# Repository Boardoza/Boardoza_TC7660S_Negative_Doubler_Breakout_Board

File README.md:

# Boardoza TC7660S Negative Doubler Breakout Board

The **Boardoza TC7660S Negative Doubler Breakout Board** is a compact voltage conversion solution based on the **TC7660S** charge pump IC. It is designed to generate a **stable negative voltage (-VOUT)** and a  **doubled negative voltage (-2VOUT)** from a positive input supply without requiring inductors.

Using a switched-capacitor voltage converter architecture, this board efficiently inverts and doubles the input voltage, making it ideal for low-current precision analog applications. It is especially well-suited for powering operational amplifiers, sensor signal conditioning circuits, and instrumentation systems where a clean and stable negative supply is required. With a typical output capability of up to **10 mA**, it is optimized for reference and low-power analog designs rather than high-current loads.

## [Click here to purchase!](https://www.ozdisan.com/ureticiler/boardoza)
| Front Side | Back Side |
| :---: | :---: |
|  |  |

---

## Key Features

- **Negative Voltage Generation:** Converts a single positive supply into stable negative voltage outputs.
- **Dual Output Capability:** Provides both -VOUT and -2VOUT options for flexible circuit design.
- **High Efficiency Charge Pump:** Achieves very high efficiency under light load conditions.
- **Low Power Consumption:** Optimized for precision, low-current applications.
- **Precision Focused Design:** Ideal for clean and stable reference voltage generation.

---

## Technical Specifications

**Model:** TC7660S-NegativeDoubler  
**Manufacturer:** Boardoza   
**Manufacturer IC:** Microchip Technology Inc.  
**Functions:** Negative voltage regulator  
**Input Voltage:** 1.5 V – 12 V  
**Voltage Input Type:** 2.50 mm pin header  
**Output Current:** 10 mA  
**Conversion Type:** Switched-capacitor charge pump  
**Oscillator Frequency:** Between 10 kHz to 45 kHz    
**Efficiency:** Up to 98–99% (typical, light load)  
**Operating Temperature:** -40 °C to +80 °C  
**Board Dimensions:** 40 mm × 20 mm

---

## Board Pinout

### ( J1 ) Power Input Connector

| Pin Number | Pin Name | Description |
| --- | --- | --- |
| 1 | VIN | Positive input voltage (1.5V – 12V) |
| 2 | GND | Ground |

### ( J2 ) Output Connector

| Pin Number | Pin Name | Description |
| --- | --- | --- |
| 1 | -2VOUT | Negative output, twice the input voltage |
| 2 | GND | Ground |
| 3 | -VOUT | Negative output, equal to input voltage |

---

## Board Dimensions

---

## Step Files

[Boardoza TC7660S-NegativeDoubler.step](./assets/TC7660S-NegativeDoubler%20Step.step)

---

## Datasheet

[TC7660S Datasheet.pdf](./assets/TC7660S-NegativeDoubler%20Datasheet.pdf)

---

## Version History

- V1.0.0 – Initial Release

---

## Support

- If you have any questions or need support, please contact **support@boardoza.com**

---

## **License**
### **Hardware Design**

[![CC BY-SA 4.0][cc-by-sa-shield]][cc-by-sa]

All hardware design files are licensed under [Creative Commons Attribution-ShareAlike 4.0 International License][cc-by-sa].

[cc-by-sa]: http://creativecommons.org/licenses/by-sa/4.0/
[cc-by-sa-shield]: https://img.shields.io/badge/License-CC%20BY--SA%204.0-lightgrey.svg

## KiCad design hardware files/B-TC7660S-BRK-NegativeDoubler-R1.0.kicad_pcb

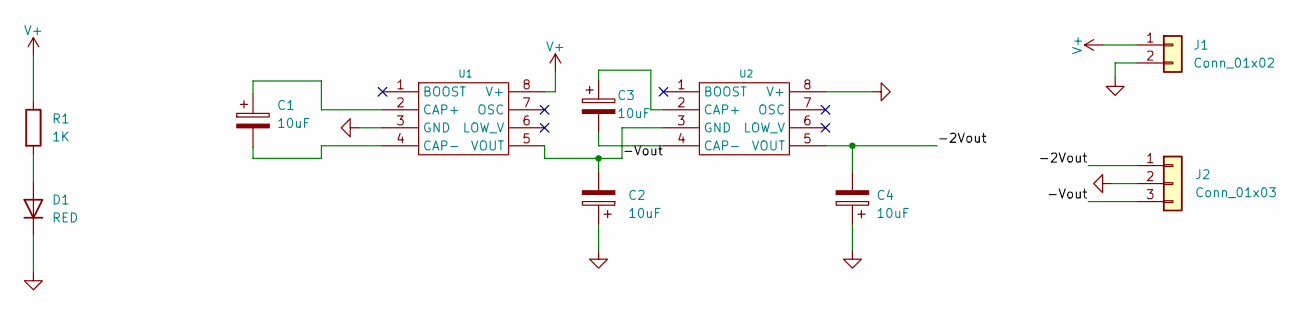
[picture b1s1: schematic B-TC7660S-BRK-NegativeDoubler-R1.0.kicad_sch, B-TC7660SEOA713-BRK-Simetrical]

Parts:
C1, C2, C3, C4: 10uF; CP_Elec_6.3x5.4; MPN JCS1H100M063054
D1: RED; D_0603_1608Metric; MPN LTST-C190KRKT
J1: Conn_01x02; 2317-02S_1x02_P2.50mm_Vertical; MPN 2317-02S
J2: Conn_01x03; 2317-03S_1x03_P2.50mm_Vertical; MPN 2317-03S
R1: 1K; R_0603_1608Metric; MPN PS03W4F1001T5E
U1, U2: SOIC127P599X175-8N; MPN TC7660SEOA713

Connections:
/-2Vout: C4.2, J2.1, U2.5 (VOUT)
/-Vout: C2.2, J2.3, U1.5 (VOUT), U2.3 (GND)
GND: C2.1, C4.1, D1.1 (K), J1.2, J2.2, U1.3 (GND), U2.8 (V+)
unnamed: D1.2 (A), R1.2
unnamed: C1.1, U1.2 (CAP+)
unnamed: C1.2, U1.4 (CAP-)
unnamed: C3.1, U2.2 (CAP+)
unnamed: C3.2, U2.4 (CAP-)
V+: J1.1, R1.1, U1.8 (V+)

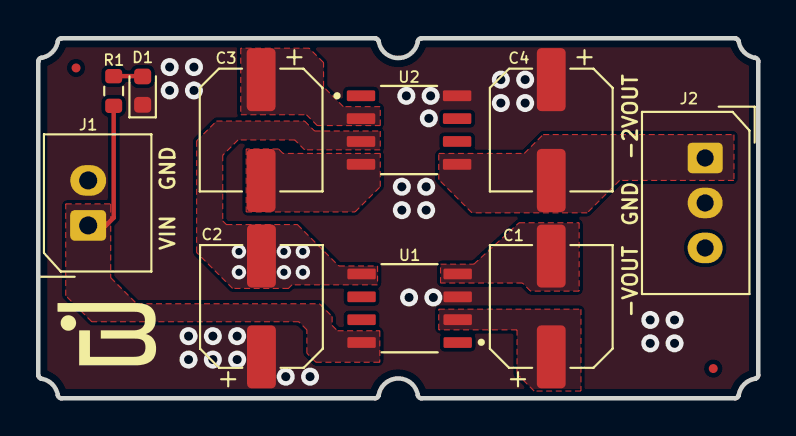
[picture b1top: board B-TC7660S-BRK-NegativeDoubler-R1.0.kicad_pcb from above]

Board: 2 copper layers, 40.0 x 20.0 mm, 10 parts (0 on the bottom side), 9 nets.
